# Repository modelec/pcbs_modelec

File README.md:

#  PCBs Modelec
Tous les PCBs de Modelec avec les librairies KiCad des composants en stock au club.

Organisation du repo :

- Une branche par année
- Un dossier par projet KiCad avec les sym-lib-table et fp-lib-table qui pointent vers la librairie modelec en chemin relatif
- Une release par PCB une fois terminé avec les fichiers de fabrications utilisés dans la commande
- Une documentation pour les PCB (complète bien sûr ;)) ici https://modelec.github.io/Documentations

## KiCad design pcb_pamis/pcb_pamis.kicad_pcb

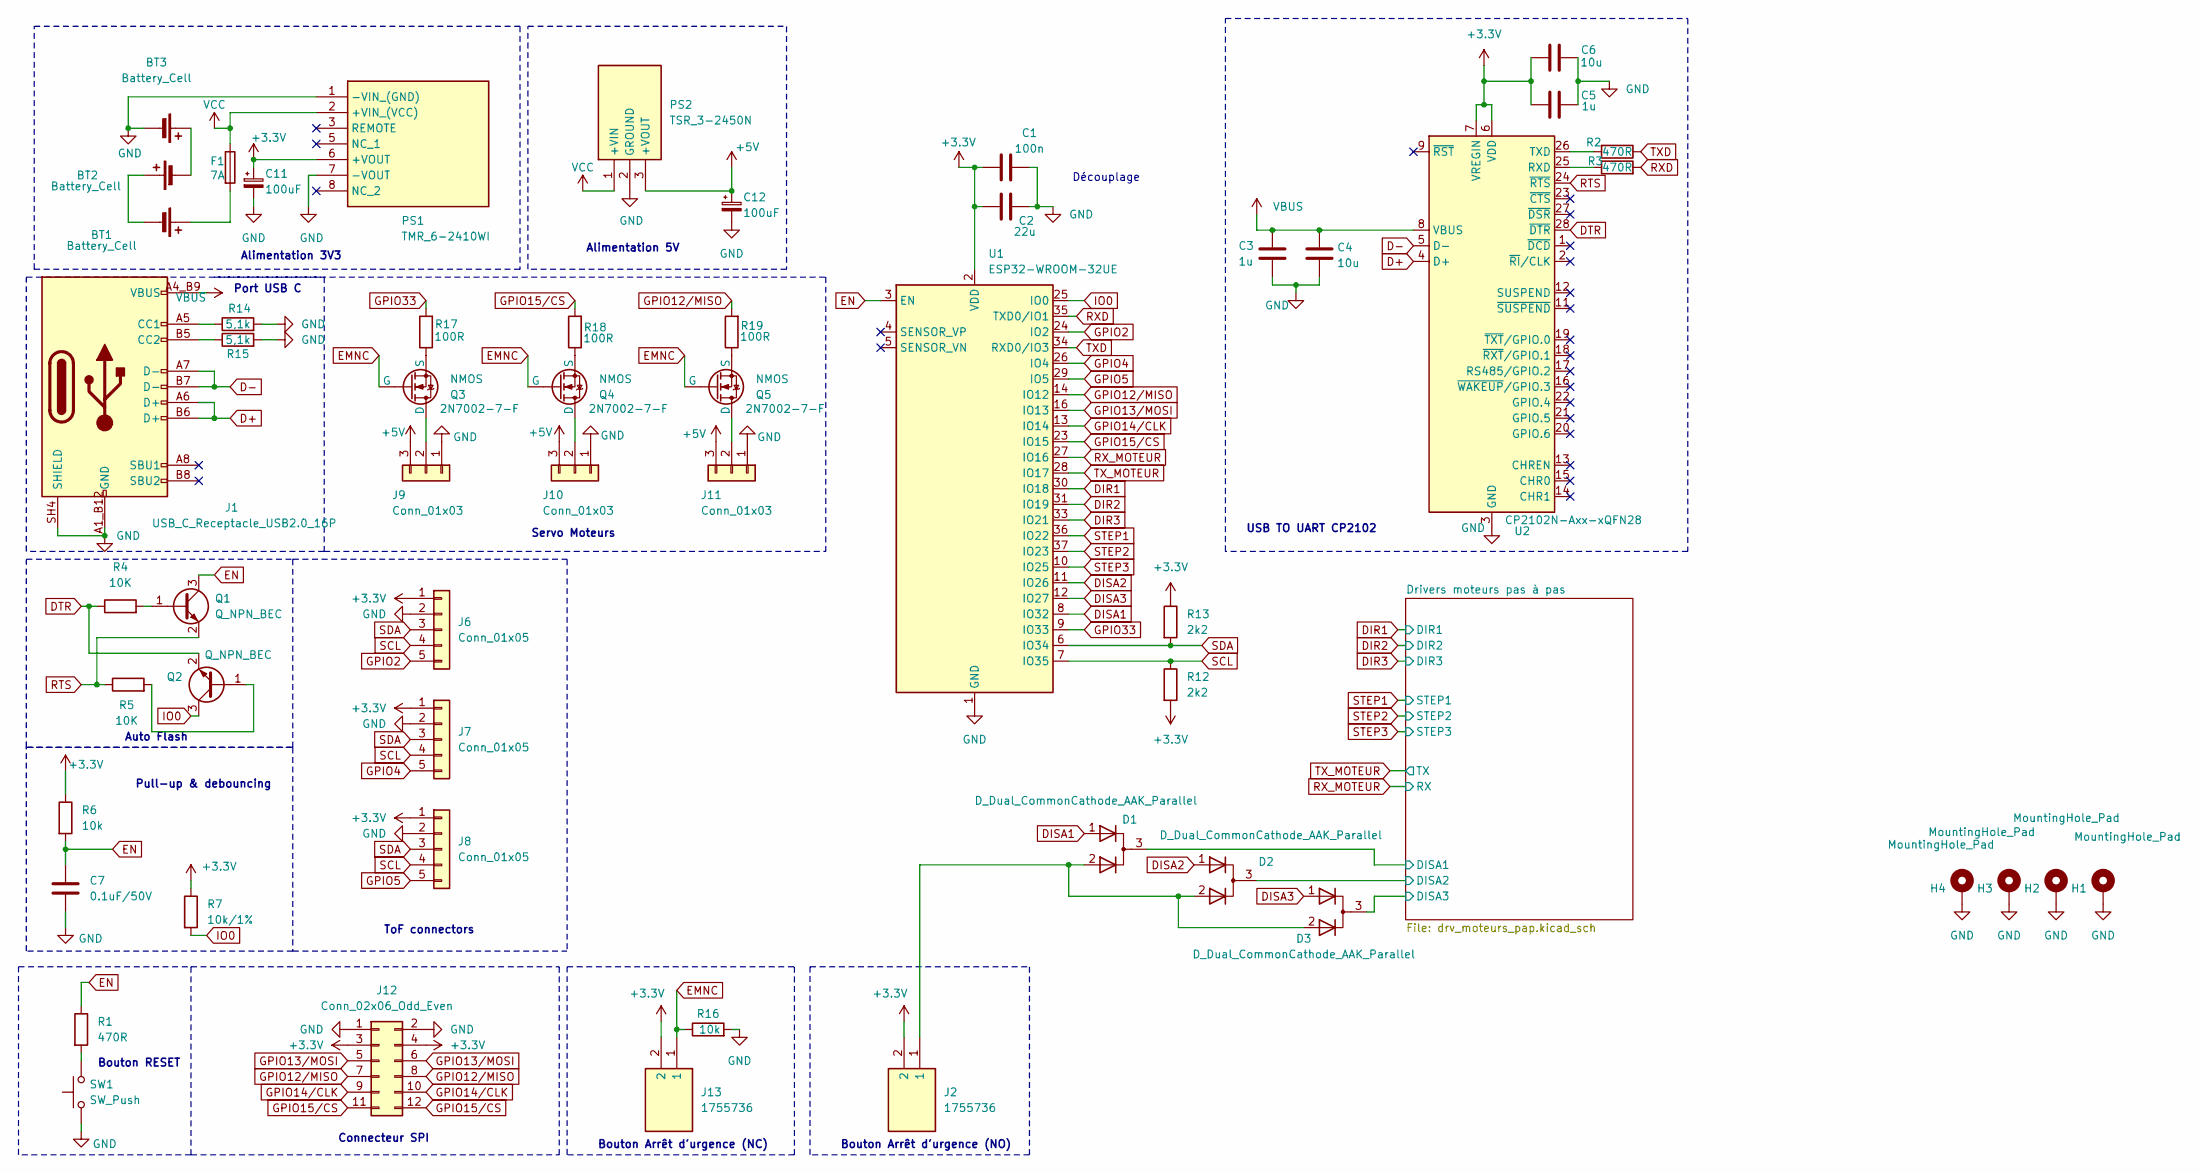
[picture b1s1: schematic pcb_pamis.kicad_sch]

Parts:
BT1, BT2, BT3: Battery_Cell; BAT_1051_CR123A
C1: 100n; C_0805_2012Metric_Pad1.18x1.45mm_HandSolder
C2: 22u; C_1206_3216Metric_Pad1.33x1.80mm_HandSolder
C3, C5: 1u; C_0805_2012Metric_Pad1.18x1.45mm_HandSolder
C4, C6: 10u; C_0805_2012Metric_Pad1.18x1.45mm_HandSolder
C7: 0.1uF/50V; C_0805_2012Metric_Pad1.18x1.45mm_HandSolder
C11, C12: 100uF; C_Radial_D6.3mm_H11.0mm_P2.50mm
D1, D2, D3: D_Dual_CommonCathode_AAK_Parallel; TSOT-23_HandSoldering
F1: 7A; 01550900M
H1, H2, H3, H4: MountingHole_Pad; MountingHole_3.2mm_M3_Pad
J1: USB_C_Receptacle_USB2.0_16P; GCT_USB4105-GF-A
J2, J13: 1755736; PhoenixContact_MSTBVA_2,5_2-G-5,08_1x02_P5.08mm_Vertical; Manufacturer_Part_Number 1755736; Mouser Part Number 651-1755736
J6, J7, J8: Conn_01x05; PinHeader_1x05_P2.54mm_Vertical
J9, J10, J11: Conn_01x03; PinHeader_1x03_P2.54mm_Vertical
J12: Conn_02x06_Odd_Even; PinHeader_2x06_P2.54mm_Vertical
PS1: TMR_6-2410WI; TMR60510; Manufacturer_Part_Number TMR 6-0510; Mouser Part Number 495-TMR6-0510
PS2: TSR_3-2450N; TSR32450N; Manufacturer_Part_Number TSR 3-2450N; Mouser Part Number 495-TSR3-2450N
Q1, Q2: Q_NPN_BEC; SOT-23_Handsoldering
Q3, Q4, Q5: NMOS; SOT-23; Manufacturer_Part_Number 2N7002-7-F
R1, R2, R3: 470R; R_0805_2012Metric_Pad1.20x1.40mm_HandSolder
R4, R5: 10K; R_0805_2012Metric_Pad1.20x1.40mm_HandSolder
R6, R16: 10k; R_0805_2012Metric_Pad1.20x1.40mm_HandSolder
R7: 10k/1%; R_0805_2012Metric_Pad1.20x1.40mm_HandSolder
R12, R13: 2k2; R_0805_2012Metric_Pad1.20x1.40mm_HandSolder
R14, R15: 5,1k; R_0805_2012Metric_Pad1.20x1.40mm_HandSolder
R17, R18, R19: 100R; R_0805_2012Metric_Pad1.20x1.40mm_HandSolder
SW1: SW_Push; SW_PUSH_6mm_H4.3mm
U1: ESP32-WROOM-32UE
U2: CP2102N-Axx-xQFN28; QFN-28-1EP_5x5mm_P0.5mm_EP3.35x3.35mm

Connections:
+3.3V: C1.1, C2.1, C5.2, C6.2, C11.1, J2.2, J6.1, J7.1, J8.1, J12.3, J12.4, J13.2, PS1.6 (+VOUT), R6.1, R7.1, R12.2, R13.1, U1.2 (VDD), U2.6 (VDD), U2.7 (VREGIN); also elsewhere on the board
+5V: C12.1, J9.3, J10.3, J11.3, PS2.3 (+VOUT)
/Drivers moteurs pas à pas/DISA1: D1.3 (K); also elsewhere on the board
/Drivers moteurs pas à pas/DISA2: D2.3 (K); also elsewhere on the board
/Drivers moteurs pas à pas/DISA3: D3.3 (K); also elsewhere on the board
D+: J1.A6 (D+), J1.B6 (D+), U2.4 (D+)
D-: J1.A7 (D-), J1.B7 (D-), U2.5 (D-)
DIR1: U1.30 (IO18); also elsewhere on the board
DIR2: U1.31 (IO19); also elsewhere on the board
DIR3: U1.33 (IO21); also elsewhere on the board
DISA1: D1.1 (A), U1.8 (IO32)
DISA2: D2.1 (A), U1.11 (IO26)
DISA3: D3.1 (A), U1.12 (IO27)
DTR: Q2.2 (E), R4.1, U2.28 (~DTR)
EMNC: J13.1, Q3.2 (G), Q4.2 (G), Q5.2 (G), R16.1
EN: C7.1, Q1.3 (C), R1.1, R6.2, U1.3 (EN)
GND: BT3.N (-), C1.2, C2.2, C3.1, C4.1, C5.1, C6.1, C7.2, C11.2, C12.2, H1.1, H2.1, H3.1, H4.1, J1.A1_B12 (GND), J1.B1_A12 (GND), J1.SH1 (SHIELD), J1.SH2 (SHIELD), J1.SH3 (SHIELD), J1.SH4 (SHIELD), J6.2, J7.2, J8.2, J9.1, J10.1, J11.1, J12.1, J12.2, PS1.1 (-VIN_(GND)), PS1.7 (-VOUT), PS2.2 (GROUND), R14.2, R15.2, R16.2, SW1.1, U1.1 (GND), U1.15 (GND), U1.38 (GND), U1.39 (GND), U2.3 (GND), U2.29 (GND); also elsewhere on the board
GPIO2: J6.5, U1.24 (IO2)
GPIO4: J7.5, U1.26 (IO4)
GPIO5: J8.5, U1.29 (IO5)
GPIO12/MISO: J12.7, J12.8, R19.2, U1.14 (IO12)
GPIO13/MOSI: J12.5, J12.6, U1.16 (IO13)
GPIO14/CLK: J12.9, J12.10, U1.13 (IO14)
GPIO15/CS: J12.11, J12.12, R18.2, U1.23 (IO15)
GPIO33: R17.2, U1.9 (IO33)
IO0: Q2.3 (C), R7.2, U1.25 (IO0)
unnamed: BT1.P (+), F1.2
unnamed: BT1.N (-), BT2.P (+)
unnamed: BT2.N (-), BT3.P (+)
unnamed: D1.2 (A), D2.2 (A), D3.2 (A), J2.1
unnamed: J1.A5 (CC1), R14.1
unnamed: J1.B5 (CC2), R15.1
unnamed: J9.2, Q3.3 (D)
unnamed: J10.2, Q4.3 (D)
unnamed: J11.2, Q5.3 (D)
unnamed: Q1.1 (B), R4.2
unnamed: Q2.1 (B), R5.2
unnamed: Q3.1 (S), R17.1
unnamed: Q4.1 (S), R18.1
unnamed: Q5.1 (S), R19.1
unnamed: R1.2, SW1.2
unnamed: R3.1, U2.25 (RXD)
unnamed: R2.2, U2.26 (TXD)
RTS: Q1.2 (E), R5.1, U2.24 (~RTS)
RXD: R3.2, U1.35 (TXD0/IO1)
RX_MOTEUR: U1.27 (IO16); also elsewhere on the board
SCL: J6.4, J7.4, J8.4, R12.1, U1.7 (IO35)
SDA: J6.3, J7.3, J8.3, R13.2, U1.6 (IO34)
STEP1: U1.36 (IO22); also elsewhere on the board
STEP2: U1.37 (IO23); also elsewhere on the board
STEP3: U1.10 (IO25); also elsewhere on the board
TXD: R2.1, U1.34 (RXD0/IO3)
TX_MOTEUR: U1.28 (IO17); also elsewhere on the board
VBUS: C3.2, C4.2, J1.A4_B9 (VBUS), J1.B4_A9 (VBUS), U2.8 (VBUS)
VCC: F1.1, PS1.2 (+VIN_(VCC)), PS2.1 (+VIN); also elsewhere on the board

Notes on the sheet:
Auto Flash
Connecteur SPI
Bouton Arrêt d'urgence (NO)
Bouton RESET
Port USB C
Pull-up & debouncing
Alimentation 3V3
Servo Moteurs
USB TO UART CP2102
Bouton Arrêt d'urgence (NC)
Découplage
ToF connectors
Alimentation 5V

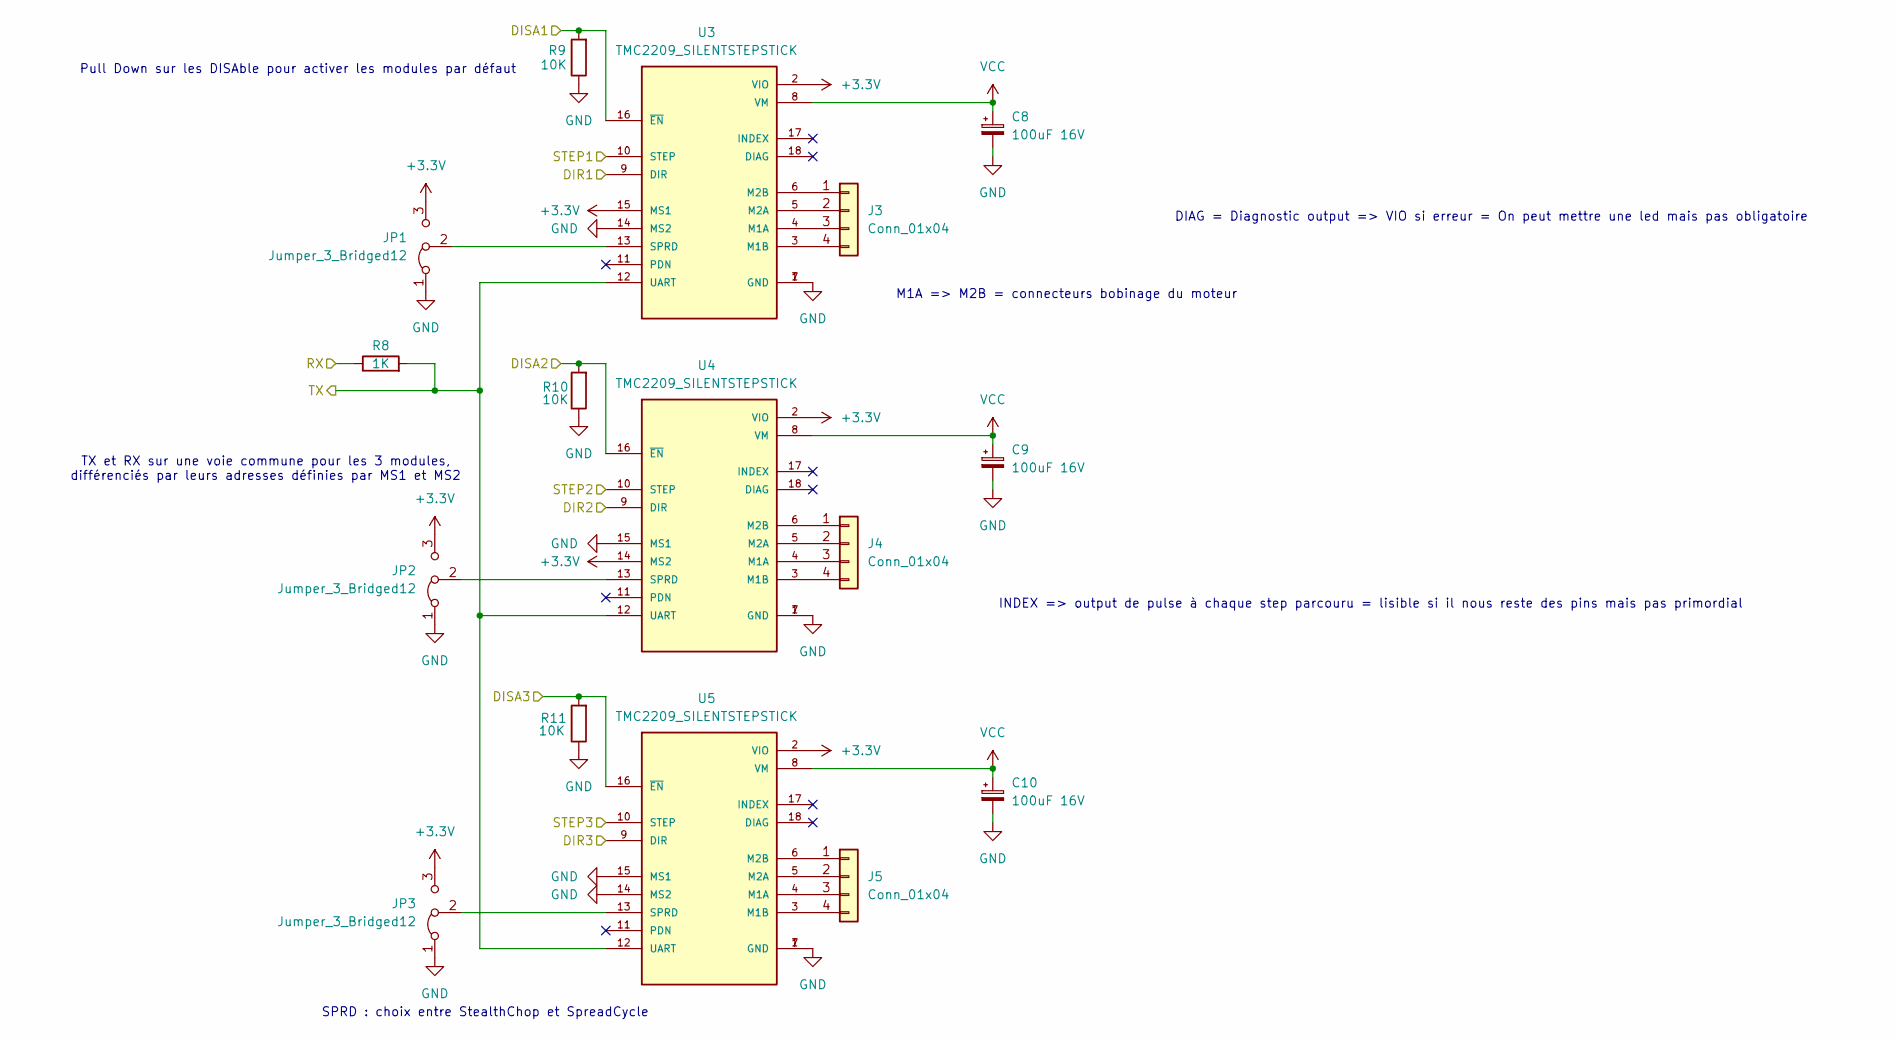
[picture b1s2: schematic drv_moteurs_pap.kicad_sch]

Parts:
C8, C9, C10: 100uF 16V; CP_6.3x11mm_horiz-L
J3, J4, J5: Conn_01x04; PinHeader_1x04_P2.54mm_Vertical
JP1, JP2, JP3: Jumper_3_Bridged12; PinHeader_1x03_P2.54mm_Vertical
R8: 1K; R_0805_2012Metric_Pad1.20x1.40mm_HandSolder
R9, R10, R11: 10K; R_0805_2012Metric_Pad1.20x1.40mm_HandSolder
U3, U4, U5: TMC2209_SILENTSTEPSTICK; MODULE_TMC2209_SILENTSTEPSTICK; PARTREV 1.20

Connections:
+3.3V: JP1.3 (B), JP2.3 (B), JP3.3 (B), U3.2 (VIO), U3.15 (MS1), U4.2 (VIO), U4.14 (MS2), U5.2 (VIO); also elsewhere on the board
/Drivers moteurs pas à pas/DISA1: R9.2, U3.16 (~EN); also elsewhere on the board
/Drivers moteurs pas à pas/DISA2: R10.2, U4.16 (~EN); also elsewhere on the board
/Drivers moteurs pas à pas/DISA3: R11.2, U5.16 (~EN); also elsewhere on the board
DIR1: U3.9 (DIR); also elsewhere on the board
DIR2: U4.9 (DIR); also elsewhere on the board
DIR3: U5.9 (DIR); also elsewhere on the board
GND: C8.2, C9.2, C10.2, JP1.1 (A), JP2.1 (A), JP3.1 (A), R9.1, R10.1, R11.1, U3.1 (GND), U3.7 (GND), U3.14 (MS2), U4.1 (GND), U4.7 (GND), U4.15 (MS1), U5.1 (GND), U5.7 (GND), U5.14 (MS2), U5.15 (MS1); also elsewhere on the board
unnamed: J3.1, U3.6 (M2B)
unnamed: J3.2, U3.5 (M2A)
unnamed: J3.3, U3.4 (M1A)
unnamed: J3.4, U3.3 (M1B)
unnamed: J4.1, U4.6 (M2B)
unnamed: J4.2, U4.5 (M2A)
unnamed: J4.3, U4.4 (M1A)
unnamed: J4.4, U4.3 (M1B)
unnamed: J5.1, U5.6 (M2B)
unnamed: J5.2, U5.5 (M2A)
unnamed: J5.3, U5.4 (M1A)
unnamed: J5.4, U5.3 (M1B)
unnamed: JP1.2 (C), U3.13 (SPRD)
unnamed: JP2.2 (C), U4.13 (SPRD)
unnamed: JP3.2 (C), U5.13 (SPRD)
RX_MOTEUR: R8.1; also elsewhere on the board
STEP1: U3.10 (STEP); also elsewhere on the board
STEP2: U4.10 (STEP); also elsewhere on the board
STEP3: U5.10 (STEP); also elsewhere on the board
TX_MOTEUR: R8.2, U3.12 (UART), U4.12 (UART), U5.12 (UART); also elsewhere on the board
VCC: C8.1, C9.1, C10.1, U3.8 (VM), U4.8 (VM), U5.8 (VM); also elsewhere on the board

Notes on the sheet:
M1A => M2B = connecteurs bobinage du moteur
INDEX => output de pulse à chaque step parcouru = lisible si il nous reste des pins mais pas primordial
DIAG = Diagnostic output => VIO si erreur = On peut mettre une led mais pas obligatoire
TX et RX sur une voie commune pour les 3 modules, différenciés par leurs adresses définies par MS1 et MS2
SPRD : choix entre StealthChop et SpreadCycle
Pull Down sur les DISAble pour activer les modules par défaut

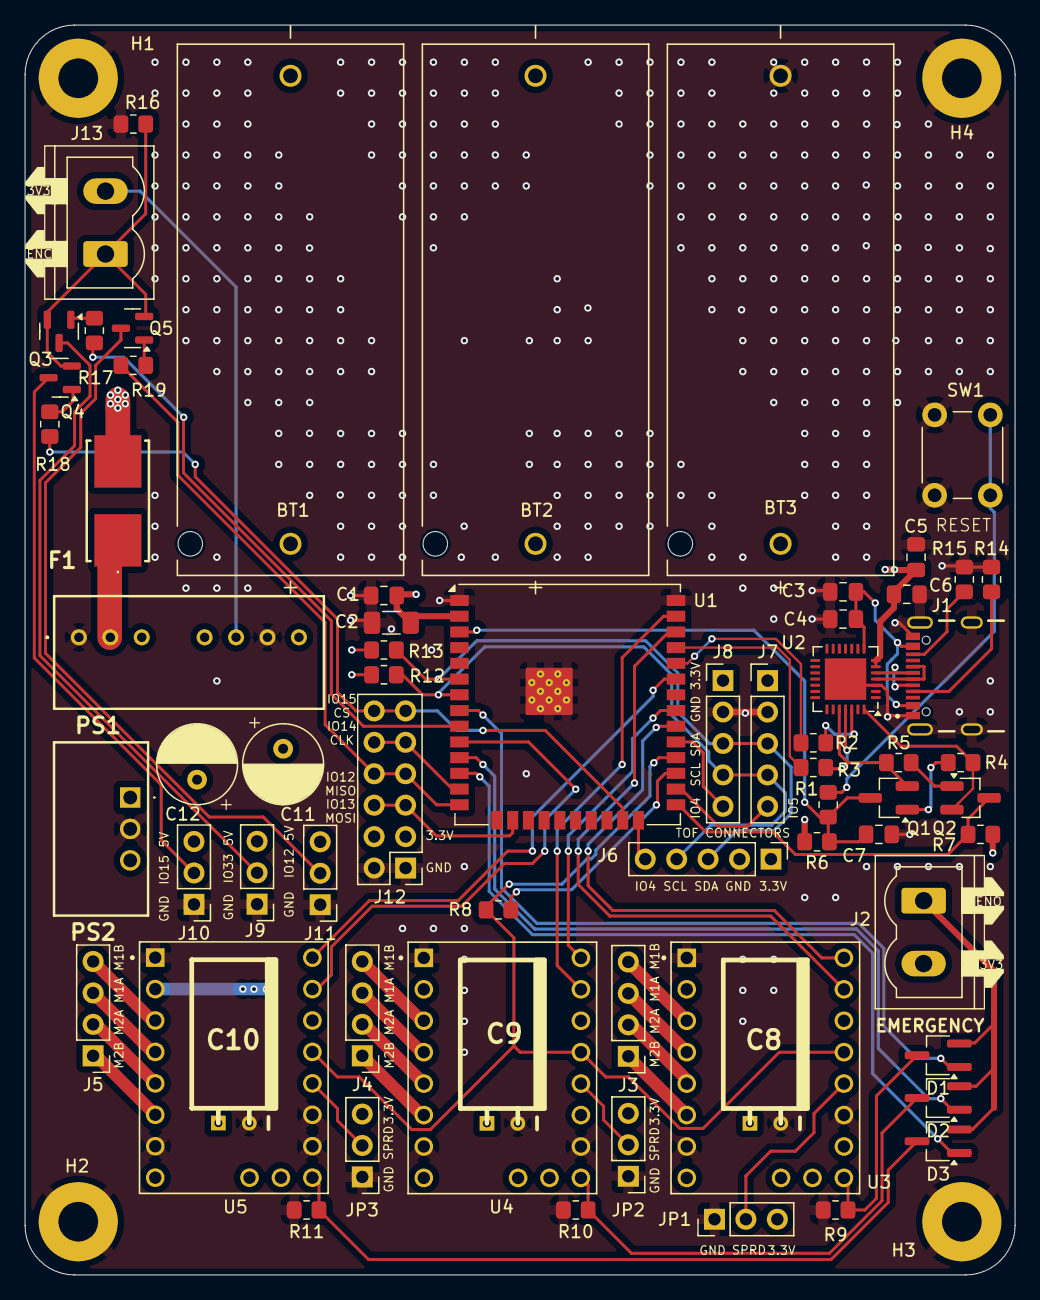
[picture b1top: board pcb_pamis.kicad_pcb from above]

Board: 4 copper layers, 80.0 x 101.0 mm, 71 parts (0 on the bottom side), 70 nets.

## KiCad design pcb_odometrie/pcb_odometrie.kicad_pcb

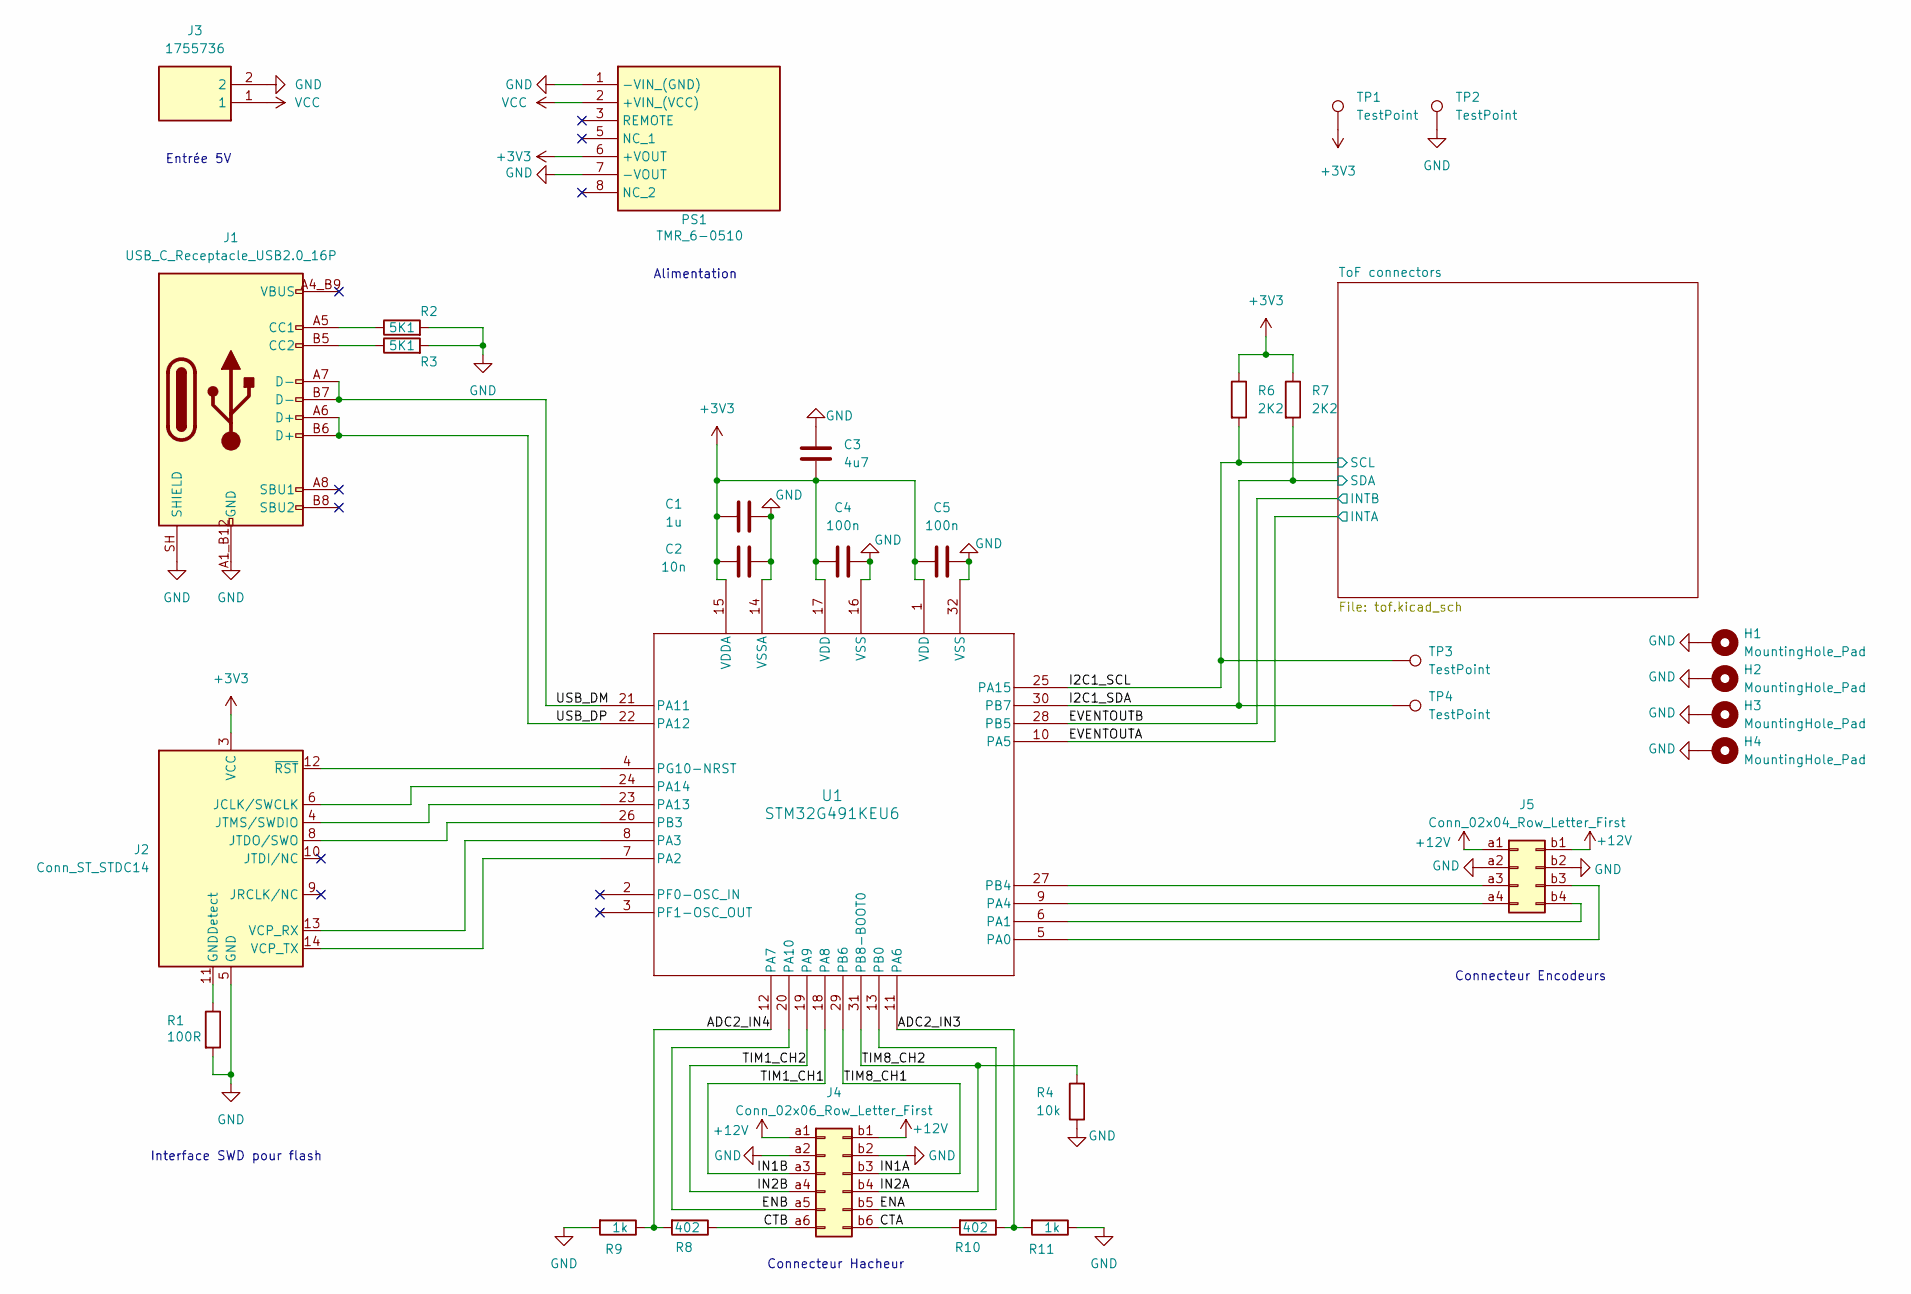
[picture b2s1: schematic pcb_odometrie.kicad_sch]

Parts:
C1: 1u; C_0805_2012Metric_Pad1.18x1.45mm_HandSolder; Manufacturer_Part_Number VJ0805Y105KXQTW1BC
C2: 10n; C_0805_2012Metric_Pad1.18x1.45mm_HandSolder; Manufacturer_Part_Number VJ0805Y103KXAMC
C3: 4u7; C_0805_2012Metric_Pad1.18x1.45mm_HandSolder; Manufacturer_Part_Number VJ0805G475KXQTW1BC
C4, C5: 100n; C_0805_2012Metric_Pad1.18x1.45mm_HandSolder; Manufacturer_Part_Number VJ0805Y104KXAMR
H1, H2, H3, H4: MountingHole_Pad; MountingHole_3.2mm_M3_ISO14580_Pad_TopBottom
J1: USB_C_Receptacle_USB2.0_16P; GCT_USB4105-GF-A
J2: Conn_ST_STDC14; CONN14_3220-14_CNC; Manufacturer_Part_Number 3220-14-0100-00
J3: 1755736; PhoenixContact_MSTBVA_2,5_2-G-5,08_1x02_P5.08mm_Vertical; Manufacturer_Part_Number 1755736; Mouser Part Number 651-1755736
J4: Conn_02x06_Row_Letter_First; PinSocket_2x06_P2.54mm_Vertical
J5: Conn_02x04_Row_Letter_First; PinHeader_2x04_P1.27mm_Vertical
PS1: TMR_6-0510; TMR60510; Manufacturer_Part_Number TMR 6-0510; Mouser Part Number 495-TMR6-0510
R1: 100R; R_0805_2012Metric_Pad1.20x1.40mm_HandSolder; Manufacturer_Part_Number CRCW0805100RFKEA
R2, R3: 5K1; R_0805_2012Metric_Pad1.20x1.40mm_HandSolder
R4: 10k; R_0805_2012Metric_Pad1.20x1.40mm_HandSolder; Manufacturer_Part_Number CRCW080510K0FKEA
R6, R7: 2K2; R_0805_2012Metric_Pad1.20x1.40mm_HandSolder
R8, R10: 402; R_0805_2012Metric_Pad1.20x1.40mm_HandSolder; Manufacturer_Part_Number CRCW080510K0FKEA
R9, R11: 1k; R_0805_2012Metric_Pad1.20x1.40mm_HandSolder; Manufacturer_Part_Number CRCW080510K0FKEA
TP1, TP2, TP3, TP4: TestPoint; TestPoint_Bridge_Pitch2.54mm_Drill0.7mm
U1: STM32G491KEU6

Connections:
+3V3: C1.1, C2.1, C3.1, C4.1, C5.1, J2.3 (VCC), PS1.6 (+VOUT), R6.1, R7.1, TP1.1, U1.1 (VDD), U1.15 (VDDA), U1.17 (VDD); also elsewhere on the board
+12V: J4.a1, J4.b1, J5.a1, J5.b1
/ADC2_IN3: R10.1, R11.2, U1.11 (PA6)
/ADC2_IN4: R8.2, R9.1, U1.12 (PA7)
/CTA: J4.b6, R10.2
/CTB: J4.a6, R8.1
/ENA: J4.b5, U1.13 (PB0)
/ENB: J4.a5, U1.20 (PA10)
/EVENTOUTA: U1.10 (PA5); also elsewhere on the board
/EVENTOUTB: U1.28 (PB5); also elsewhere on the board
/I2C1_SCL: R6.2, TP3.1, U1.25 (PA15); also elsewhere on the board
/I2C1_SDA: R7.2, TP4.1, U1.30 (PB7); also elsewhere on the board
/IN1A: J4.b3, U1.29 (PB6)
/IN1B: J4.a3, U1.18 (PA8)
/IN2A: J4.b4, R4.2, U1.31 (PB8-BOOT0)
/IN2B: J4.a4, U1.19 (PA9)
/USB_DM: J1.A7 (D-), J1.B7 (D-), U1.21 (PA11)
/USB_DP: J1.A6 (D+), J1.B6 (D+), U1.22 (PA12)
GND: C1.2, C2.2, C3.2, C4.2, C5.2, H1.1, H2.1, H3.1, H4.1, J1.A1_B12 (GND), J1.B1_A12 (GND), J1.SH (SHIELD), J2.5 (GND), J2.7 (GND), J3.2, J4.a2, J4.b2, J5.a2, J5.b2, PS1.1 (-VIN_(GND)), PS1.7 (-VOUT), R1.2, R2.2, R3.2, R4.1, R9.2, R11.1, TP2.1, U1.14 (VSSA), U1.16 (VSS), U1.32 (VSS); also elsewhere on the board
unnamed: J1.A5 (CC1), R2.1
unnamed: J1.B5 (CC2), R3.1
unnamed: J2.11 (GNDDetect), R1.1
unnamed: J2.6 (JCLK/SWCLK), U1.24 (PA14)
unnamed: J2.8 (JTDO/SWO), U1.26 (PB3)
unnamed: J2.4 (JTMS/SWDIO), U1.23 (PA13)
unnamed: J2.13 (VCP_RX), U1.8 (PA3)
unnamed: J2.14 (VCP_TX), U1.7 (PA2)
unnamed: J2.12 (~RST), U1.4 (PG10-NRST)
unnamed: J5.a3, U1.27 (PB4)
unnamed: J5.a4, U1.9 (PA4)
unnamed: J5.b3, U1.5 (PA0)
unnamed: J5.b4, U1.6 (PA1)
VCC: J3.1, PS1.2 (+VIN_(VCC)); also elsewhere on the board

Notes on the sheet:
Connecteur Encodeurs
Entrée 5V
Alimentation
Connecteur Hacheur
Interface SWD pour flash

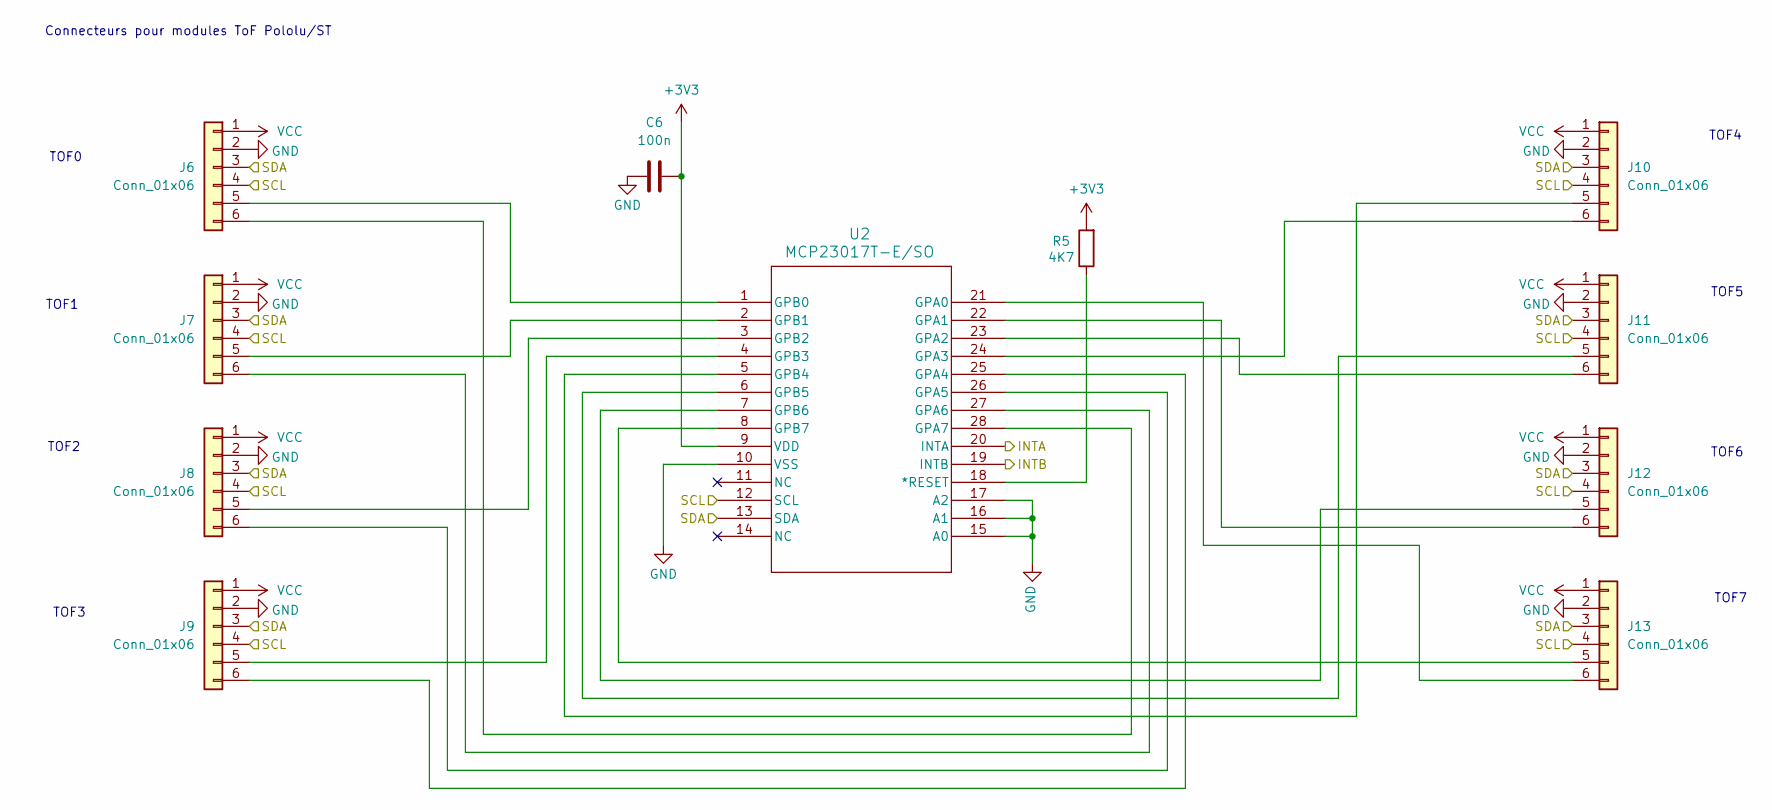
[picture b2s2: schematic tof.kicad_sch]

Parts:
C6: 100n; C_0805_2012Metric_Pad1.18x1.45mm_HandSolder
J6, J7, J8, J9, J10, J11, J12, J13: Conn_01x06; PinHeader_1x06_P1.27mm_Vertical
R5: 4K7; R_0805_2012Metric_Pad1.20x1.40mm_HandSolder
U2: MCP23017T-E/SO; SOIC28-W_MC_MCH

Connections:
+3V3: C6.2, R5.2, U2.9 (VDD); also elsewhere on the board
/EVENTOUTA: U2.20 (INTA); also elsewhere on the board
/EVENTOUTB: U2.19 (INTB); also elsewhere on the board
/I2C1_SCL: J6.4, J7.4, J8.4, J9.4, J10.4, J11.4, J12.4, J13.4, U2.12 (SCL); also elsewhere on the board
/I2C1_SDA: J6.3, J7.3, J8.3, J9.3, J10.3, J11.3, J12.3, J13.3, U2.13 (SDA); also elsewhere on the board
GND: C6.1, J6.2, J7.2, J8.2, J9.2, J10.2, J11.2, J12.2, J13.2, U2.10 (VSS), U2.15 (A0), U2.16 (A1), U2.17 (A2); also elsewhere on the board
unnamed: J6.5, U2.1 (GPB0)
unnamed: J6.6, U2.28 (GPA7)
unnamed: J7.5, U2.2 (GPB1)
unnamed: J7.6, U2.27 (GPA6)
unnamed: J8.5, U2.3 (GPB2)
unnamed: J8.6, U2.26 (GPA5)
unnamed: J9.5, U2.4 (GPB3)
unnamed: J9.6, U2.25 (GPA4)
unnamed: J10.5, U2.5 (GPB4)
unnamed: J10.6, U2.24 (GPA3)
unnamed: J11.5, U2.6 (GPB5)
unnamed: J11.6, U2.23 (GPA2)
unnamed: J12.5, U2.7 (GPB6)
unnamed: J12.6, U2.22 (GPA1)
unnamed: J13.5, U2.8 (GPB7)
unnamed: J13.6, U2.21 (GPA0)
unnamed: R5.1, U2.18 (*RESET)
VCC: J6.1, J7.1, J8.1, J9.1, J10.1, J11.1, J12.1, J13.1; also elsewhere on the board

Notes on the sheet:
TOF3
TOF6
TOF7
TOF2
TOF0
Connecteurs pour modules ToF Pololu/ST
TOF1
TOF4
TOF5

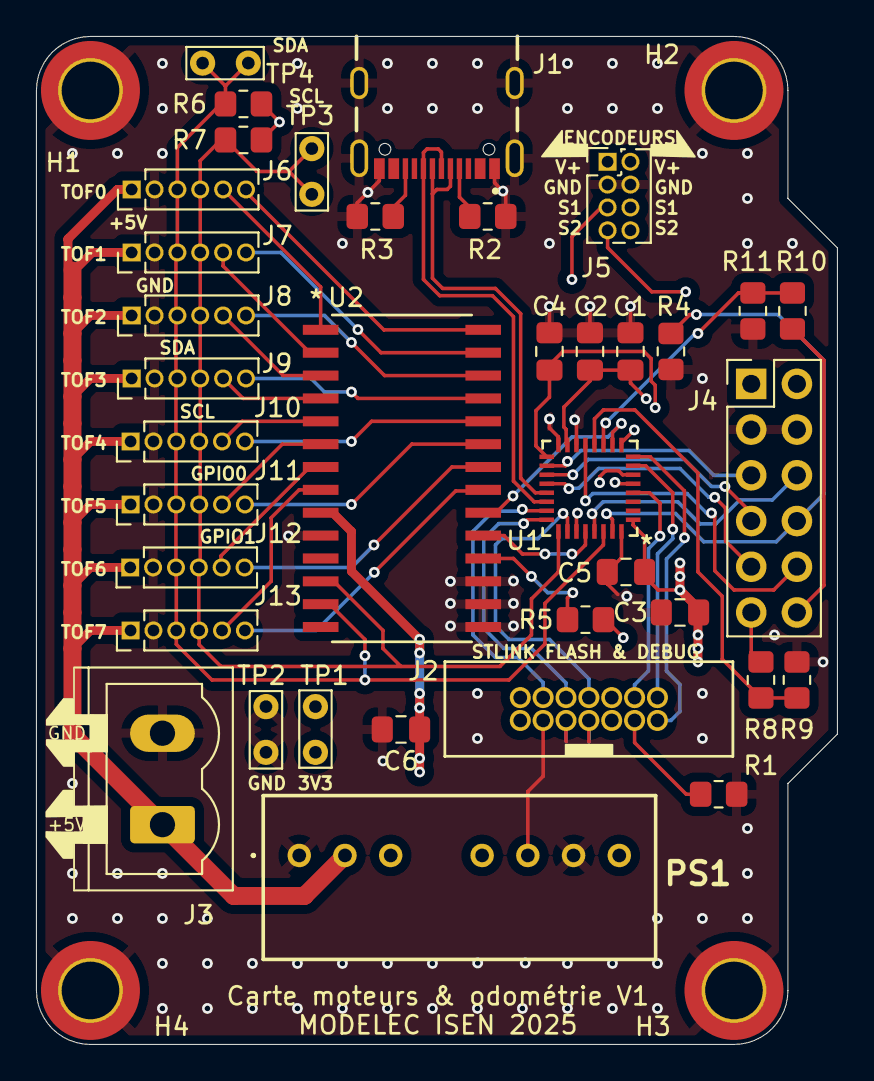
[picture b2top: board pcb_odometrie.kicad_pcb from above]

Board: 4 copper layers, 44.5 x 56.0 mm, 41 parts (0 on the bottom side), 50 nets.

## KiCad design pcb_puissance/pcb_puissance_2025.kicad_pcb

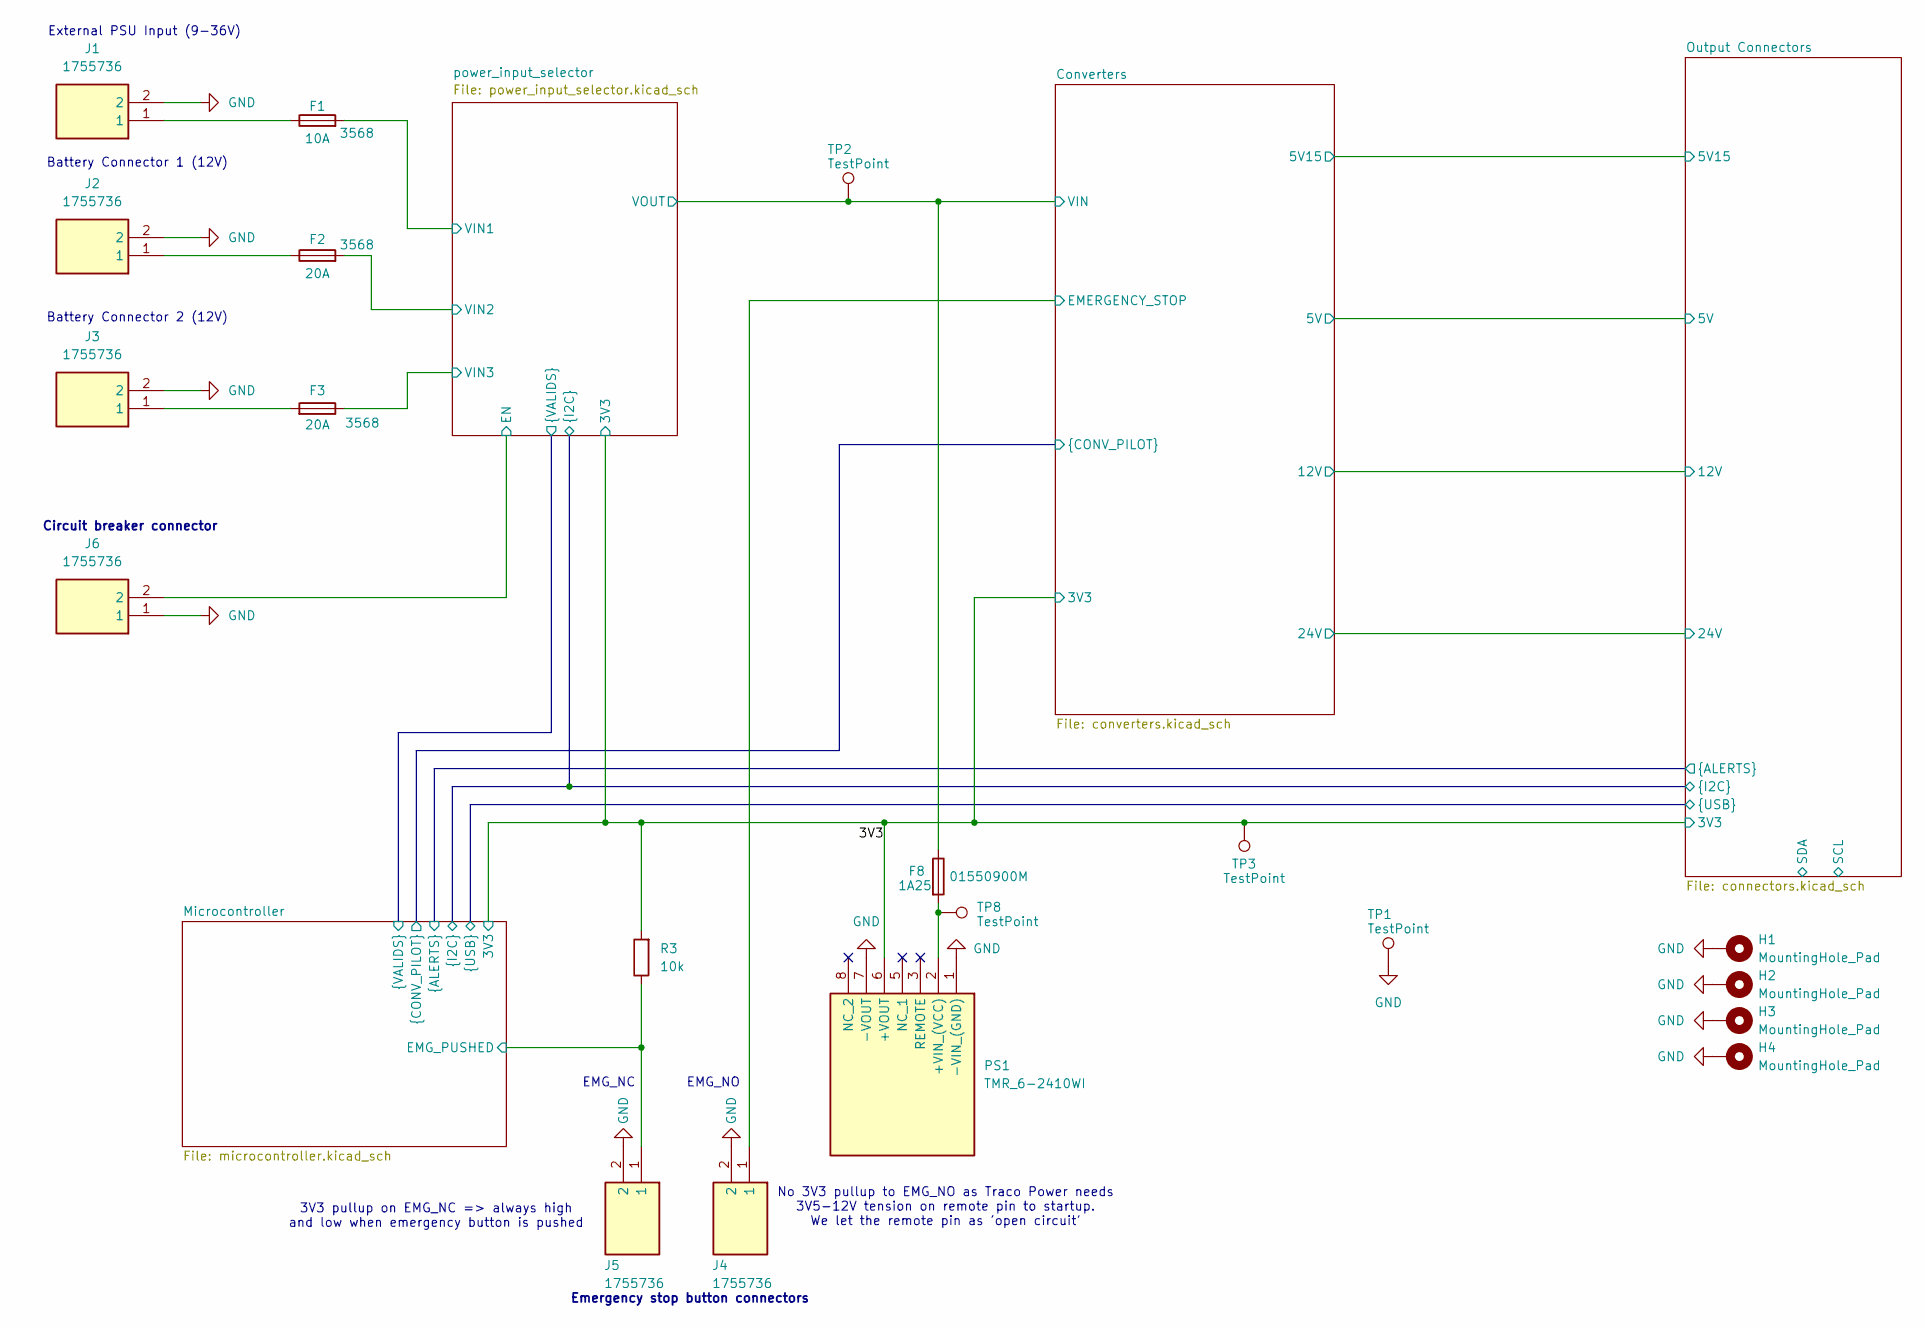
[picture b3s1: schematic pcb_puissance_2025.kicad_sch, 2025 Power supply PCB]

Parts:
F1: 10A; Fuseholder_Blade_Mini_Keystone_3568; Manufacturer_Part_Number 3568
F2, F3: 20A; Fuseholder_Blade_Mini_Keystone_3568; Manufacturer_Part_Number 3568
F8: 1A25; 01550900M; Manufacturer_Part_Number 01550900M
H1, H2, H3, H4: MountingHole_Pad; MountingHole_3.2mm_M3_ISO14580_Pad_TopBottom
J1, J2, J3, J4, J5, J6: 1755736; PhoenixContact_MSTBVA_2,5_2-G-5,08_1x02_P5.08mm_Vertical; Manufacturer_Part_Number 1755736; Mouser Part Number 651-1755736
PS1: TMR_6-2410WI; TMR60510; Manufacturer_Part_Number TMR_6-2410WI; Mouser Part Number 495-TMR6-0510
R3: 10k; R_0805_2012Metric_Pad1.20x1.40mm_HandSolder; Manufacturer_Part_Number CRCW080510K0FKEA
TP1, TP2, TP3, TP8: TestPoint; TestPoint_Pad_D1.5mm

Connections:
/3V3: PS1.6 (+VOUT), R3.2, TP3.1; also elsewhere on the board
/Converters/EMERGENCY_STOP: J4.1; also elsewhere on the board
/Converters/VIN: F8.1, TP2.1; also elsewhere on the board
/Microcontroller/PA1: J5.1, R3.1; also elsewhere on the board
/power_input_selector/EN: J6.2; also elsewhere on the board
/power_input_selector/VIN1: F1.2; also elsewhere on the board
/power_input_selector/VIN2: F2.2; also elsewhere on the board
/power_input_selector/VIN3: F3.1; also elsewhere on the board
GND: H1.1, H2.1, H3.1, H4.1, J1.2, J2.2, J3.2, J4.2, J5.2, J6.1, PS1.1 (-VIN_(GND)), PS1.7 (-VOUT), TP1.1; also elsewhere on the board
unnamed: F1.1, J1.1
unnamed: F2.1, J2.1
unnamed: F3.2, J3.1
unnamed: F8.2, PS1.2 (+VIN_(VCC)), TP8.1

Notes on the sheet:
Circuit breaker connector
3V3 pullup on EMG_NC => always high and low when emergency button is pushed
Battery Connector 2 (12V)
Emergency stop button connectors
Battery Connector 1 (12V)
External PSU Input (9-36V)
No 3V3 pullup to EMG_NO as Traco Power needs 3V5-12V tension on remote pin to startup. We let the remote pin as 'open circuit'
EMG_NO
EMG_NC
